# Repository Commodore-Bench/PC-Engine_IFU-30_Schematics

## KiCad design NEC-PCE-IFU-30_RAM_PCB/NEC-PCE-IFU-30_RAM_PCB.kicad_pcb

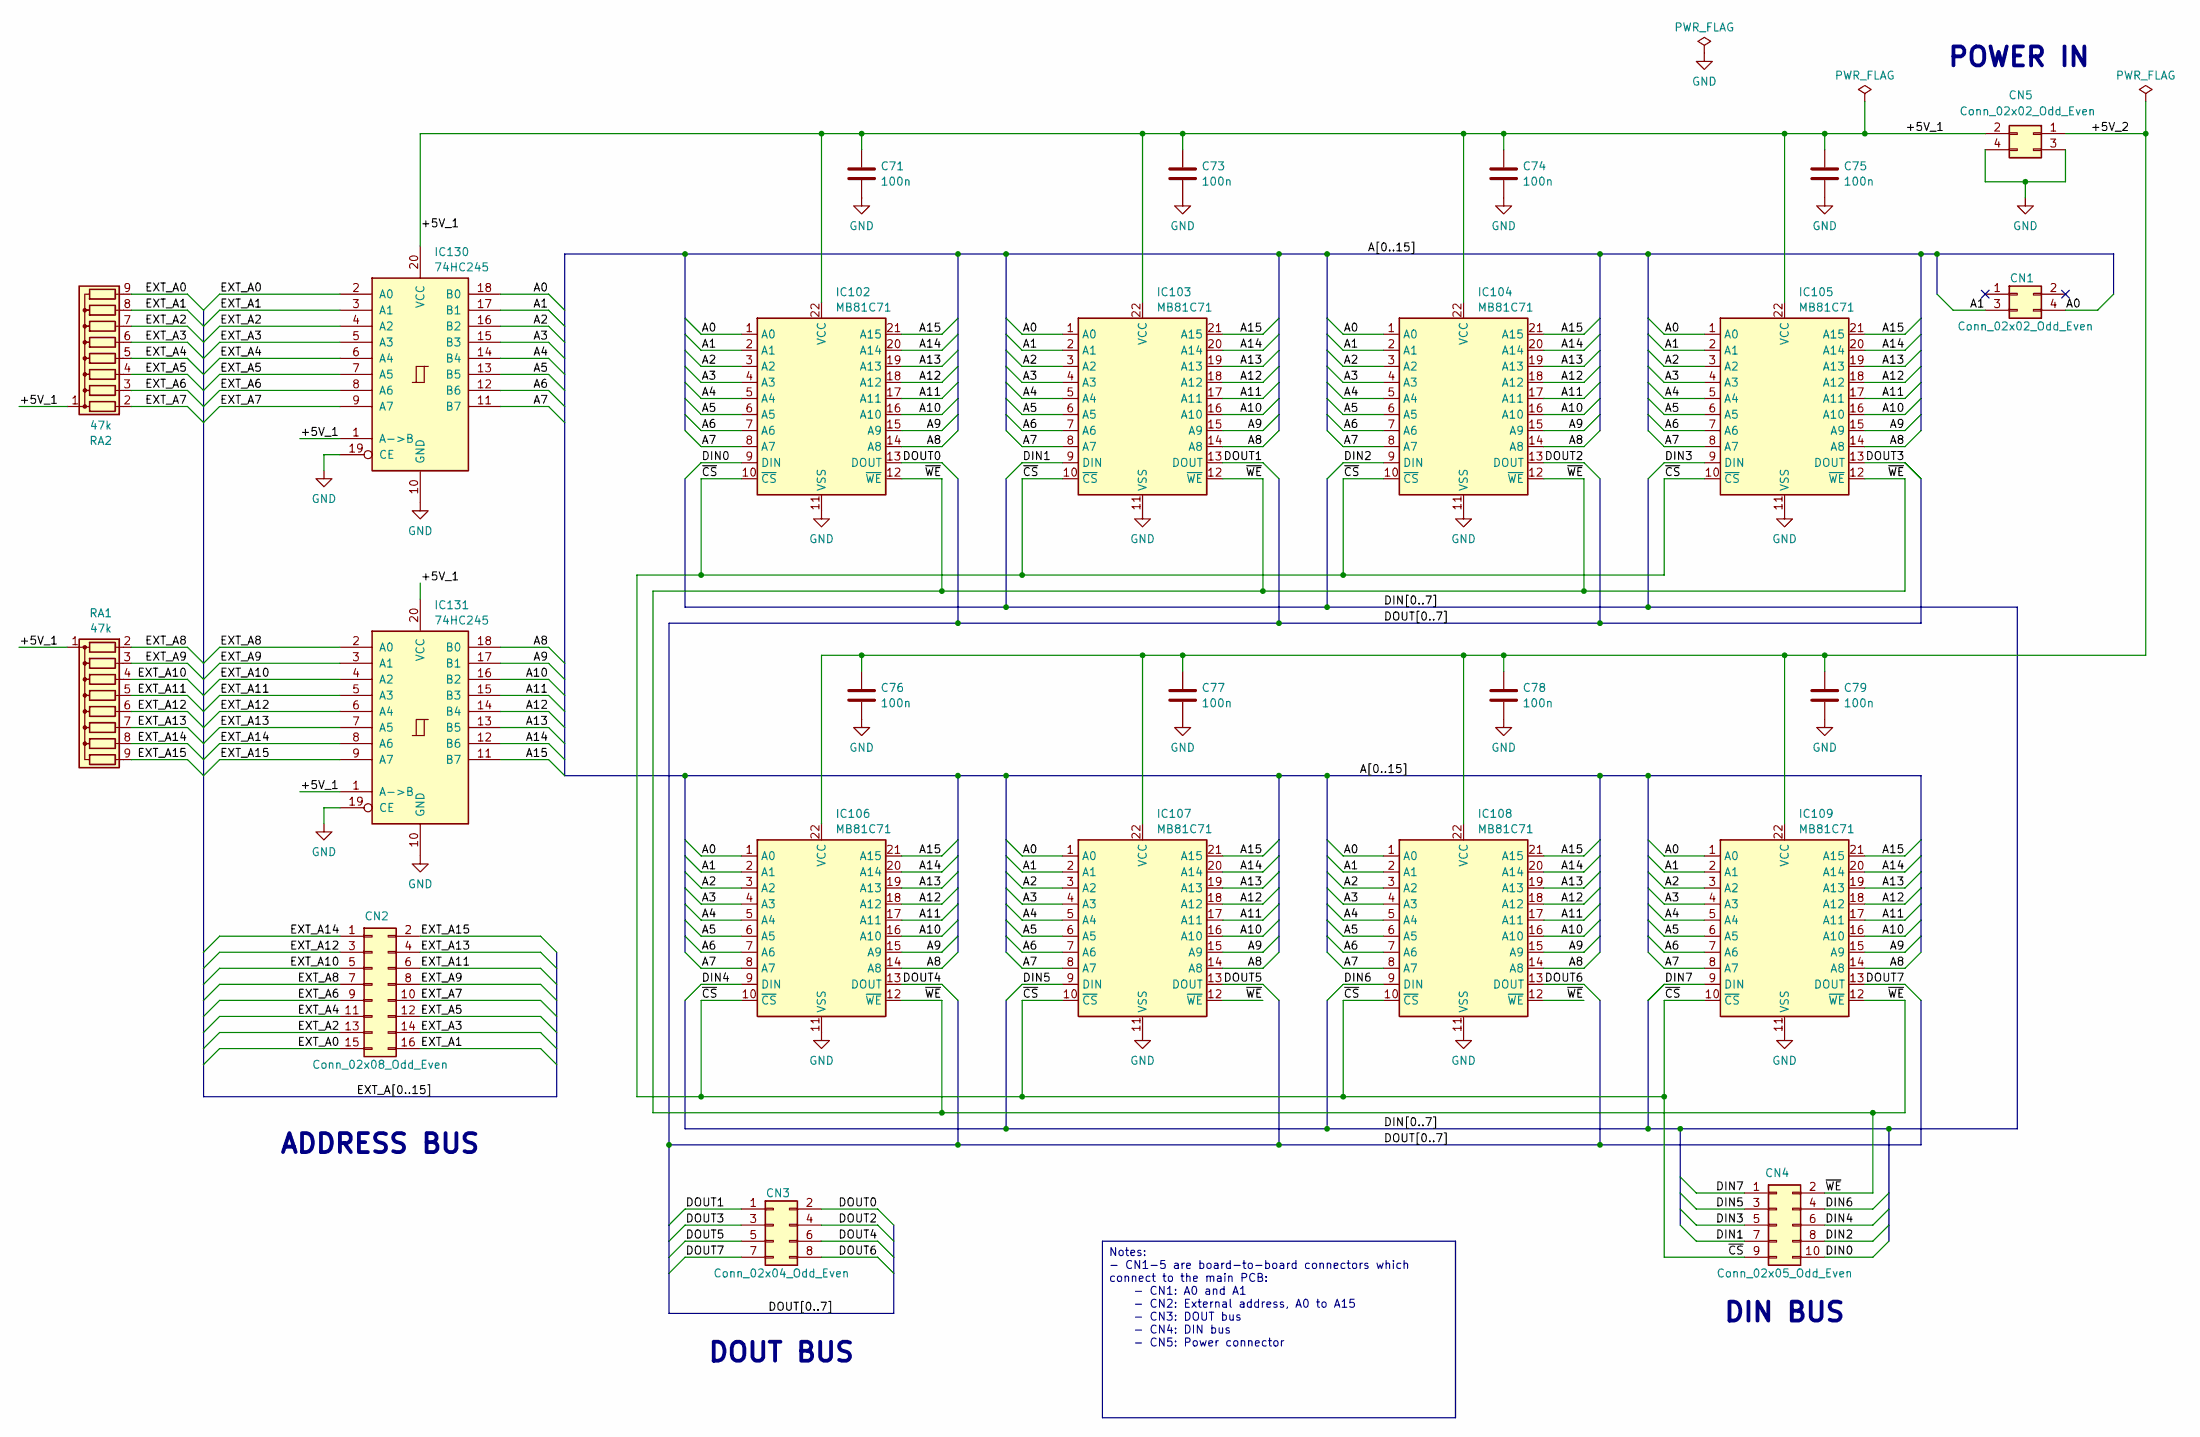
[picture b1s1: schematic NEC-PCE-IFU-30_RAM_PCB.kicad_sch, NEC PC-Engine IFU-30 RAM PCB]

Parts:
C71, C73, C74, C75, C76, C77, C78, C79: 100n; C_Disc_D3.0mm_W2.0mm_P2.50mm
CN1, CN5: Conn_02x02_Odd_Even; PinHeader_2x02_P2.54mm_Vertical
CN2: Conn_02x08_Odd_Even; PinHeader_2x08_P2.54mm_Vertical
CN3: Conn_02x04_Odd_Even; PinHeader_2x04_P2.54mm_Vertical
CN4: Conn_02x05_Odd_Even; PinHeader_2x05_P2.54mm_Vertical
IC102, IC103, IC104, IC105, IC106, IC107, IC108, IC109: MB81C71; DIP-22_W7.62mm
IC130, IC131: 74HC245; DIP-20_W7.62mm
RA1, RA2: 47k; R_Array_SIP9

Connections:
/+5V_1: C71.2, C73.2, C74.2, C75.2, CN5.2, IC102.22 (VCC), IC103.22 (VCC), IC104.22 (VCC), IC105.22 (VCC), IC130.1 (A->B), IC130.20 (VCC), IC131.1 (A->B), IC131.20 (VCC), RA1.1 (common), RA2.1 (common)
/+5V_2: C76.2, C77.2, C78.2, C79.2, CN5.1, IC106.22 (VCC), IC107.22 (VCC), IC108.22 (VCC), IC109.22 (VCC)
/A0: CN1.4, IC102.1 (A0), IC103.1 (A0), IC104.1 (A0), IC105.1 (A0), IC106.1 (A0), IC107.1 (A0), IC108.1 (A0), IC109.1 (A0), IC130.18 (B0)
/A1: CN1.3, IC102.2 (A1), IC103.2 (A1), IC104.2 (A1), IC105.2 (A1), IC106.2 (A1), IC107.2 (A1), IC108.2 (A1), IC109.2 (A1), IC130.17 (B1)
/A2: IC102.3 (A2), IC103.3 (A2), IC104.3 (A2), IC105.3 (A2), IC106.3 (A2), IC107.3 (A2), IC108.3 (A2), IC109.3 (A2), IC130.16 (B2)
/A3: IC102.4 (A3), IC103.4 (A3), IC104.4 (A3), IC105.4 (A3), IC106.4 (A3), IC107.4 (A3), IC108.4 (A3), IC109.4 (A3), IC130.15 (B3)
/A4: IC102.5 (A4), IC103.5 (A4), IC104.5 (A4), IC105.5 (A4), IC106.5 (A4), IC107.5 (A4), IC108.5 (A4), IC109.5 (A4), IC130.14 (B4)
/A5: IC102.6 (A5), IC103.6 (A5), IC104.6 (A5), IC105.6 (A5), IC106.6 (A5), IC107.6 (A5), IC108.6 (A5), IC109.6 (A5), IC130.13 (B5)
/A6: IC102.7 (A6), IC103.7 (A6), IC104.7 (A6), IC105.7 (A6), IC106.7 (A6), IC107.7 (A6), IC108.7 (A6), IC109.7 (A6), IC130.12 (B6)
/A7: IC102.8 (A7), IC103.8 (A7), IC104.8 (A7), IC105.8 (A7), IC106.8 (A7), IC107.8 (A7), IC108.8 (A7), IC109.8 (A7), IC130.11 (B7)
/A8: IC102.14 (A8), IC103.14 (A8), IC104.14 (A8), IC105.14 (A8), IC106.14 (A8), IC107.14 (A8), IC108.14 (A8), IC109.14 (A8), IC131.18 (B0)
/A9: IC102.15 (A9), IC103.15 (A9), IC104.15 (A9), IC105.15 (A9), IC106.15 (A9), IC107.15 (A9), IC108.15 (A9), IC109.15 (A9), IC131.17 (B1)
/A10: IC102.16 (A10), IC103.16 (A10), IC104.16 (A10), IC105.16 (A10), IC106.16 (A10), IC107.16 (A10), IC108.16 (A10), IC109.16 (A10), IC131.16 (B2)
/A11: IC102.17 (A11), IC103.17 (A11), IC104.17 (A11), IC105.17 (A11), IC106.17 (A11), IC107.17 (A11), IC108.17 (A11), IC109.17 (A11), IC131.15 (B3)
/A12: IC102.18 (A12), IC103.18 (A12), IC104.18 (A12), IC105.18 (A12), IC106.18 (A12), IC107.18 (A12), IC108.18 (A12), IC109.18 (A12), IC131.14 (B4)
/A13: IC102.19 (A13), IC103.19 (A13), IC104.19 (A13), IC105.19 (A13), IC106.19 (A13), IC107.19 (A13), IC108.19 (A13), IC109.19 (A13), IC131.13 (B5)
/A14: IC102.20 (A14), IC103.20 (A14), IC104.20 (A14), IC105.20 (A14), IC106.20 (A14), IC107.20 (A14), IC108.20 (A14), IC109.20 (A14), IC131.12 (B6)
/A15: IC102.21 (A15), IC103.21 (A15), IC104.21 (A15), IC105.21 (A15), IC106.21 (A15), IC107.21 (A15), IC108.21 (A15), IC109.21 (A15), IC131.11 (B7)
/DIN0: CN4.10, IC102.9 (DIN)
/DIN1: CN4.7, IC103.9 (DIN)
/DIN2: CN4.8, IC104.9 (DIN)
/DIN3: CN4.5, IC105.9 (DIN)
/DIN4: CN4.6, IC106.9 (DIN)
/DIN5: CN4.3, IC107.9 (DIN)
/DIN6: CN4.4, IC108.9 (DIN)
/DIN7: CN4.1, IC109.9 (DIN)
/DOUT0: CN3.2, IC102.13 (DOUT)
/DOUT1: CN3.1, IC103.13 (DOUT)
/DOUT2: CN3.4, IC104.13 (DOUT)
/DOUT3: CN3.3, IC105.13 (DOUT)
/DOUT4: CN3.6, IC106.13 (DOUT)
/DOUT5: CN3.5, IC107.13 (DOUT)
/DOUT6: CN3.8, IC108.13 (DOUT)
/DOUT7: CN3.7, IC109.13 (DOUT)
/EXT_A0: CN2.15, IC130.2 (A0), RA2.9 (R8)
/EXT_A1: CN2.16, IC130.3 (A1), RA2.8 (R7)
/EXT_A2: CN2.13, IC130.4 (A2), RA2.7 (R6)
/EXT_A3: CN2.14, IC130.5 (A3), RA2.6 (R5)
/EXT_A4: CN2.11, IC130.6 (A4), RA2.5 (R4)
/EXT_A5: CN2.12, IC130.7 (A5), RA2.4 (R3)
/EXT_A6: CN2.9, IC130.8 (A6), RA2.3 (R2)
/EXT_A7: CN2.10, IC130.9 (A7), RA2.2 (R1)
/EXT_A8: CN2.7, IC131.2 (A0), RA1.2 (R1)
/EXT_A9: CN2.8, IC131.3 (A1), RA1.3 (R2)
/EXT_A10: CN2.5, IC131.4 (A2), RA1.4 (R3)
/EXT_A11: CN2.6, IC131.5 (A3), RA1.5 (R4)
/EXT_A12: CN2.3, IC131.6 (A4), RA1.6 (R5)
/EXT_A13: CN2.4, IC131.7 (A5), RA1.7 (R6)
/EXT_A14: CN2.1, IC131.8 (A6), RA1.8 (R7)
/EXT_A15: CN2.2, IC131.9 (A7), RA1.9 (R8)
/~CS: CN4.9, IC102.10 (~CS), IC103.10 (~CS), IC104.10 (~CS), IC105.10 (~CS), IC106.10 (~CS), IC107.10 (~CS), IC108.10 (~CS), IC109.10 (~CS)
/~WE: CN4.2, IC102.12 (~WE), IC103.12 (~WE), IC104.12 (~WE), IC105.12 (~WE), IC106.12 (~WE), IC107.12 (~WE), IC108.12 (~WE), IC109.12 (~WE)
GND: C71.1, C73.1, C74.1, C75.1, C76.1, C77.1, C78.1, C79.1, CN5.3, CN5.4, IC102.11 (VSS), IC103.11 (VSS), IC104.11 (VSS), IC105.11 (VSS), IC106.11 (VSS), IC107.11 (VSS), IC108.11 (VSS), IC109.11 (VSS), IC130.10 (GND), IC130.19 (CE), IC131.10 (GND), IC131.19 (CE)

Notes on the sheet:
DOUT BUS
ADDRESS BUS
DIN BUS
POWER IN
Notes: - CN1-5 are board-to-board connectors which connect to the main PCB: - CN1: A0 and A1 - CN2: External address, A0 to A15 - CN3: DOUT bus - CN4: DIN bus - CN5: Power connector

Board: 2 copper layers, 25 parts (0 on the bottom side), 53 nets, no tracks yet.

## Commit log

2025-07-12 Fixed a lot of issues on data bus on the MCU page.
